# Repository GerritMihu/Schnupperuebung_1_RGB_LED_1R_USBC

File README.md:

# Schnupperuebung_1_RGB_LED_1R_USBC
 Extra leichte Übung für jüngere Schnupperer. 1 RGB LED 1 Widerstand mit USB-C
 
## Blider
TODO Bilder hier einfügen
TODO LED Richtiges 3D Model finden/erstellen

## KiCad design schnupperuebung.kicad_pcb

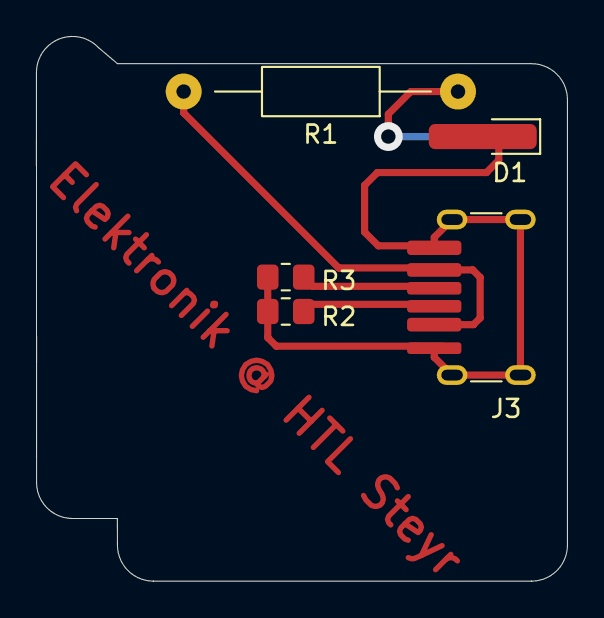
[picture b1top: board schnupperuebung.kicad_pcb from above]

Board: 2 copper layers, 29.5 x 30.3 mm, 5 parts (0 on the bottom side), 5 nets.

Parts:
D1: LED; LED_0805_2012Metric
J3: USB_C_Receptacle_PowerOnly_6P; USB_C_Receptacle_GCT_USB4125-xx-x-0190_6P_TopMnt_Horizontal
R1: 1k; R_Axial_DIN0207_L6.3mm_D2.5mm_P15.24mm_Horizontal
R2, R3: 5,1k; R_0805_2012Metric_Pad1.20x1.40mm_HandSolder

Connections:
GND: D1.1 (K), J3.A12 (GND), J3.B12 (GND), J3.S1 (SHIELD), R2.1, R3.1
unnamed: D1.2 (A), R1.1
unnamed: J3.A5 (CC1), R2.2
unnamed: J3.B5 (CC2), R3.2
VBUS: J3.A9 (VBUS), J3.B9 (VBUS), R1.2

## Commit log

2025-03-31 Files added
2025-12-15 pcb drc
2026-05-19 Updated Footprint & Created pics
2026-06-15 CAM created
